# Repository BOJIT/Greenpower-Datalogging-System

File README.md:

# Greenpower-Datalogging-System

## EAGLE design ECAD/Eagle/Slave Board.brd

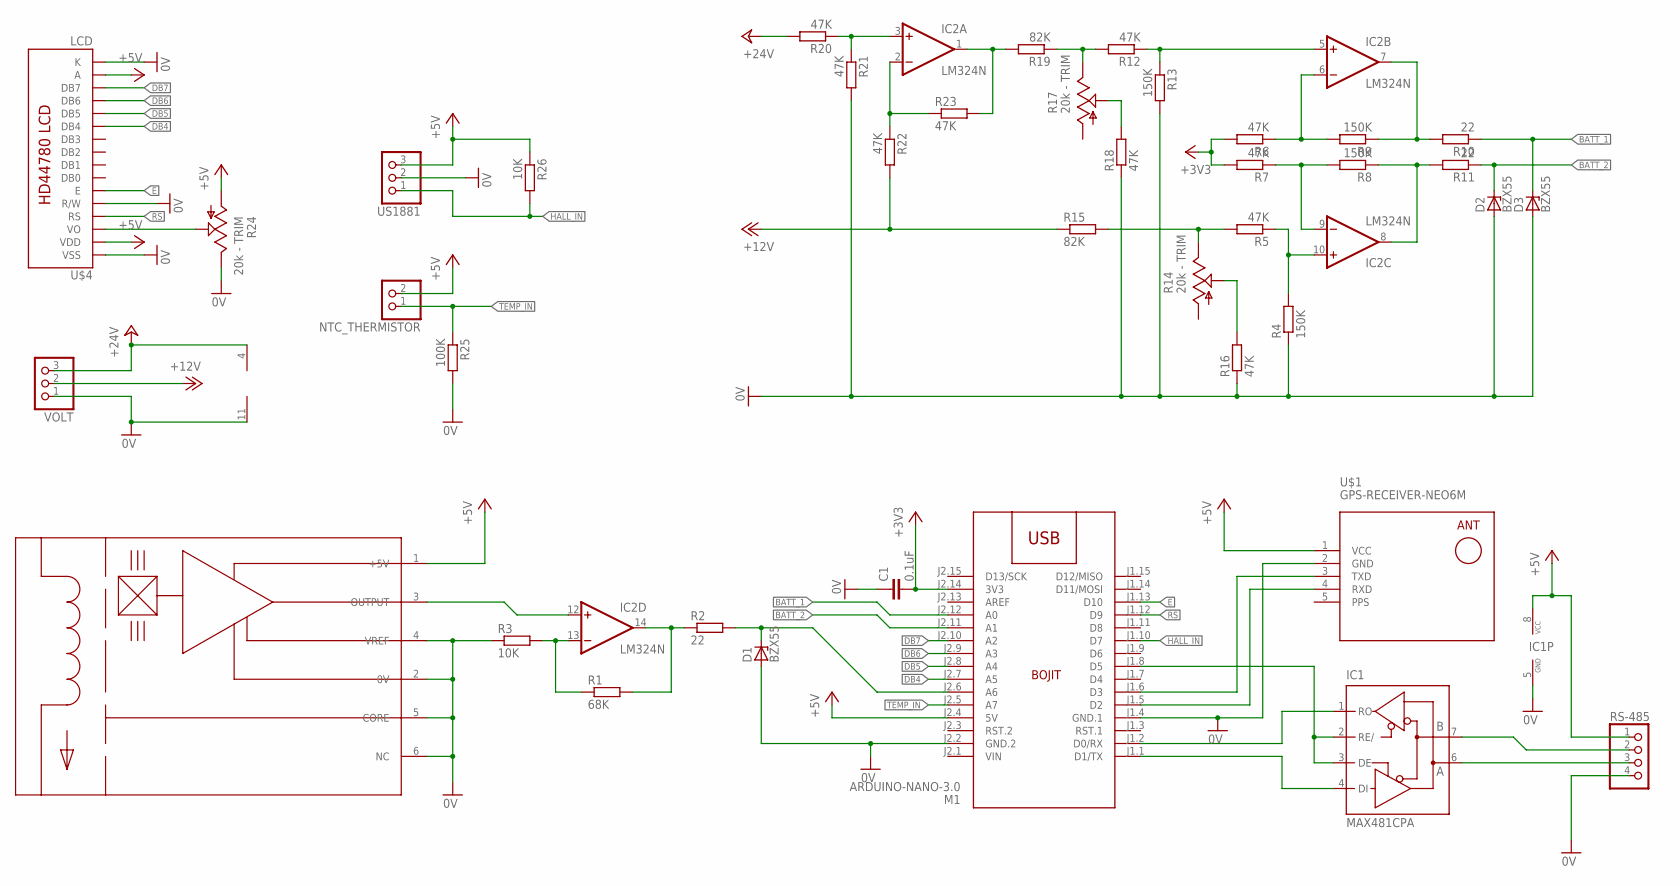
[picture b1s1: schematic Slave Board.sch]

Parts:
C1: 0.1uF; C050-030X075
D1, D2, D3: BZX55; DO35Z10
IC1: MAX481CPA; DIL08
IC2: LM324N; DIL14
M1: ARDUINO-NANO-3.0
NTC_THERMISTOR: PINHD-1X2/90; 1X02/90
R1: 68K; 0204/7
R2, R10, R11: 22; 0204/7
R3, R26: 10K; 0204/7
R4, R8, R9, R13: 150K; 0204/7
R5, R6, R7, R12, R16, R18, R20, R21, R22, R23: 47K; 0204/7
R14, R17, R24: 20k - TRIM; CA9V
R15, R19: 82K; 0204/7
R25: 100K; 0204/7
RS-485: PINHD-1X4/90; 1X04/90
U$1: GPS-RECEIVER-NEO6M
U$2: LEM_50-P
U$3: BOJIT_LARGE
U$4: LCD; LCD-16X2-4HOLES
US1881: PINHD-1X3/90; 1X03/90
VOLT: PINHD-1X3/90; 1X03/90

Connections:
0V: C1.1, D1.A, D2.A, D3.A, IC1.5 (GND), IC2.11 (V-), M1.J1.4 (GND.1), M1.J2.2 (GND.2), R3.1, R4.1, R13.2, R16.1, R18.1, R21.2, R24.E, R25.2, RS-485.4, U$1.2 (GND), U$2.2 (0V), U$2.4 (VREF), U$2.5 (CORE), U$2.6 (NC), U$4.1 (VSS), U$4.5 (R/W), U$4.16 (K), US1881.2, VOLT.1
+3V3: C1.2, M1.J2.14 (3V3), R6.2, R7.2
+5V: IC1.8 (VCC), M1.J2.4 (5V), NTC_THERMISTOR.2, R24.A, R26.1, RS-485.1, U$1.1 (VCC), U$2.1 (+5V), U$4.2 (VDD), U$4.15 (A), US1881.3
+12V: R15.1, R22.2, VOLT.2
+24V: IC2.4 (V+), R20.2, VOLT.3
BATT_1: D3.C, M1.J2.12 (A0), R10.1
BATT_2: D2.C, M1.J2.11 (A1), R11.1
DB4: M1.J2.7 (A5), U$4.11 (DB4)
DB5: M1.J2.8 (A4), U$4.12 (DB5)
DB6: M1.J2.9 (A3), U$4.13 (DB6)
DB7: M1.J2.10 (A2), U$4.14 (DB7)
E: M1.J1.13 (D10), U$4.6 (E)
HALL_IN: M1.J1.10 (D7), R26.2, US1881.1
unnamed: IC1.6 (A), RS-485.3
unnamed: IC1.7 (B), RS-485.2
unnamed: R24.S, U$4.3 (VO)
unnamed: IC1.2 (RE/), IC1.3 (DE), M1.J1.8 (D5)
unnamed: IC1.1 (RO), M1.J1.2 (D0/RX)
unnamed: IC1.4 (DI), M1.J1.1 (D1/TX)
unnamed: M1.J1.5 (D2), U$1.4 (RXD)
unnamed: M1.J1.6 (D3), U$1.3 (TXD)
unnamed: IC2.13 (-IN), R1.1, R3.2
unnamed: IC2.14 (OUT), R1.2, R2.1
unnamed: IC2.12 (+IN), U$2.3 (OUTPUT)
unnamed: D1.C, M1.J2.6 (A6), R2.2
unnamed: IC2.7 (OUT), R9.1, R10.2
unnamed: IC2.8 (OUT), R8.1, R11.2
unnamed: R14.S, R16.2
unnamed: IC2.9 (-IN), R7.1, R8.2
unnamed: IC2.6 (-IN), R6.1, R9.2
unnamed: IC2.10 (+IN), R4.2, R5.1
unnamed: IC2.5 (+IN), R12.1, R13.1
unnamed: R12.2, R17.E, R19.1
unnamed: R5.2, R14.E, R15.2
unnamed: R17.S, R18.2
unnamed: IC2.1 (OUT), R19.2, R23.2
unnamed: IC2.2 (-IN), R22.1, R23.1
unnamed: IC2.3 (+IN), R20.1, R21.1
PPS: U$1.5 (PPS)
RS: M1.J1.12 (D9), U$4.4 (RS)
TEMP_IN: M1.J2.5 (A7), NTC_THERMISTOR.1, R25.1
VIN: M1.J2.1 (VIN)

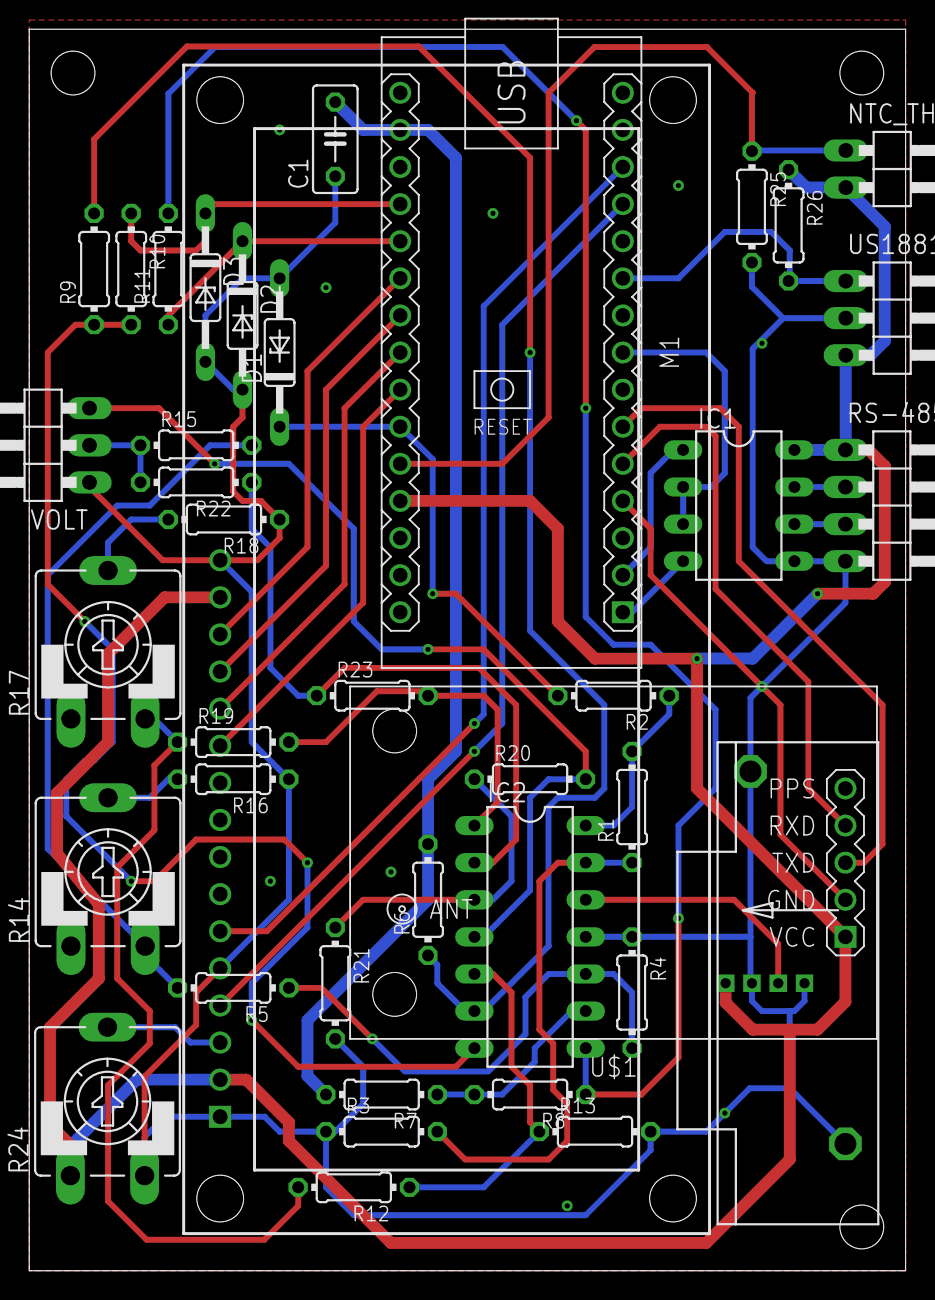
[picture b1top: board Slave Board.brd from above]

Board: 2 copper layers, 60.0 x 85.0 mm, 41 parts (0 on the bottom side), 40 nets.

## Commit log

2019-05-29 added firmware

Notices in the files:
parts and their libraries:
diy-modules: Released under the Creative Commons Attribution 4.0 International License: http://creativecommons.org/licenses/by/4.0
